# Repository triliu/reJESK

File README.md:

# reJESK

The reJESK, a redox-inspired 70-switch ortholinear keyboard that uses a new diode-free design. 

The diode-free design is easy for first-time keyboard makers, as it reduces the complexity and length of time to make your own board. This keyboard is part of the geometric diode-free keyboard project, which is creating keyboards with great key rollover characteristics without using diodes. Other keyboards released previously are the [Heawood42](https://github.com/triliu/Heawood42) (A 21*2-key split ortholinear board, with 21 keys per 14 GPIO) and the [JESK56](https://github.com/triliu/JESK56) (A 56-key monobody ortholinear board, with 56 keys using 28 GPIO). 

The diode-free design comes from a modification of the JESK graph, which was used in the [JESK56 keyboard](https://github.com/triliu/JESK56) to yield a 56-switch keyboard using 28 GPIO without diodes. This has been placed together with a design that is inspired by the [redox keyboard](https://github.com/mattdibi/redox-keyboard). The JESK graph was found by Exoo, Kolokolnikov, Janssen, Salamon; see their [arXiv paper](https://arxiv.org/abs/2307.07308) or [final publication](https://onlinelibrary.wiley.com/doi/10.1002/jgt.23146?af=R)

This repo contains:
- PCB gerbers (production files) and kicad files (PCB design files). See below for easy print instructions. 
- QMK firmware
- 3D model case 
- (soon) build guide

Many thanks to PCBway, who sponsered this project. You can easily print the reJESK keyboard using the project page on PCBway:

If you wish to modify and print the reJESK keyboard, consider using my affiliate link to help me out as I develop further boards: https://pcbway.com/g/oPKu26

"If you aren’t ready for reJESKtion, you aren’t ready for love.” – Marty Rubin

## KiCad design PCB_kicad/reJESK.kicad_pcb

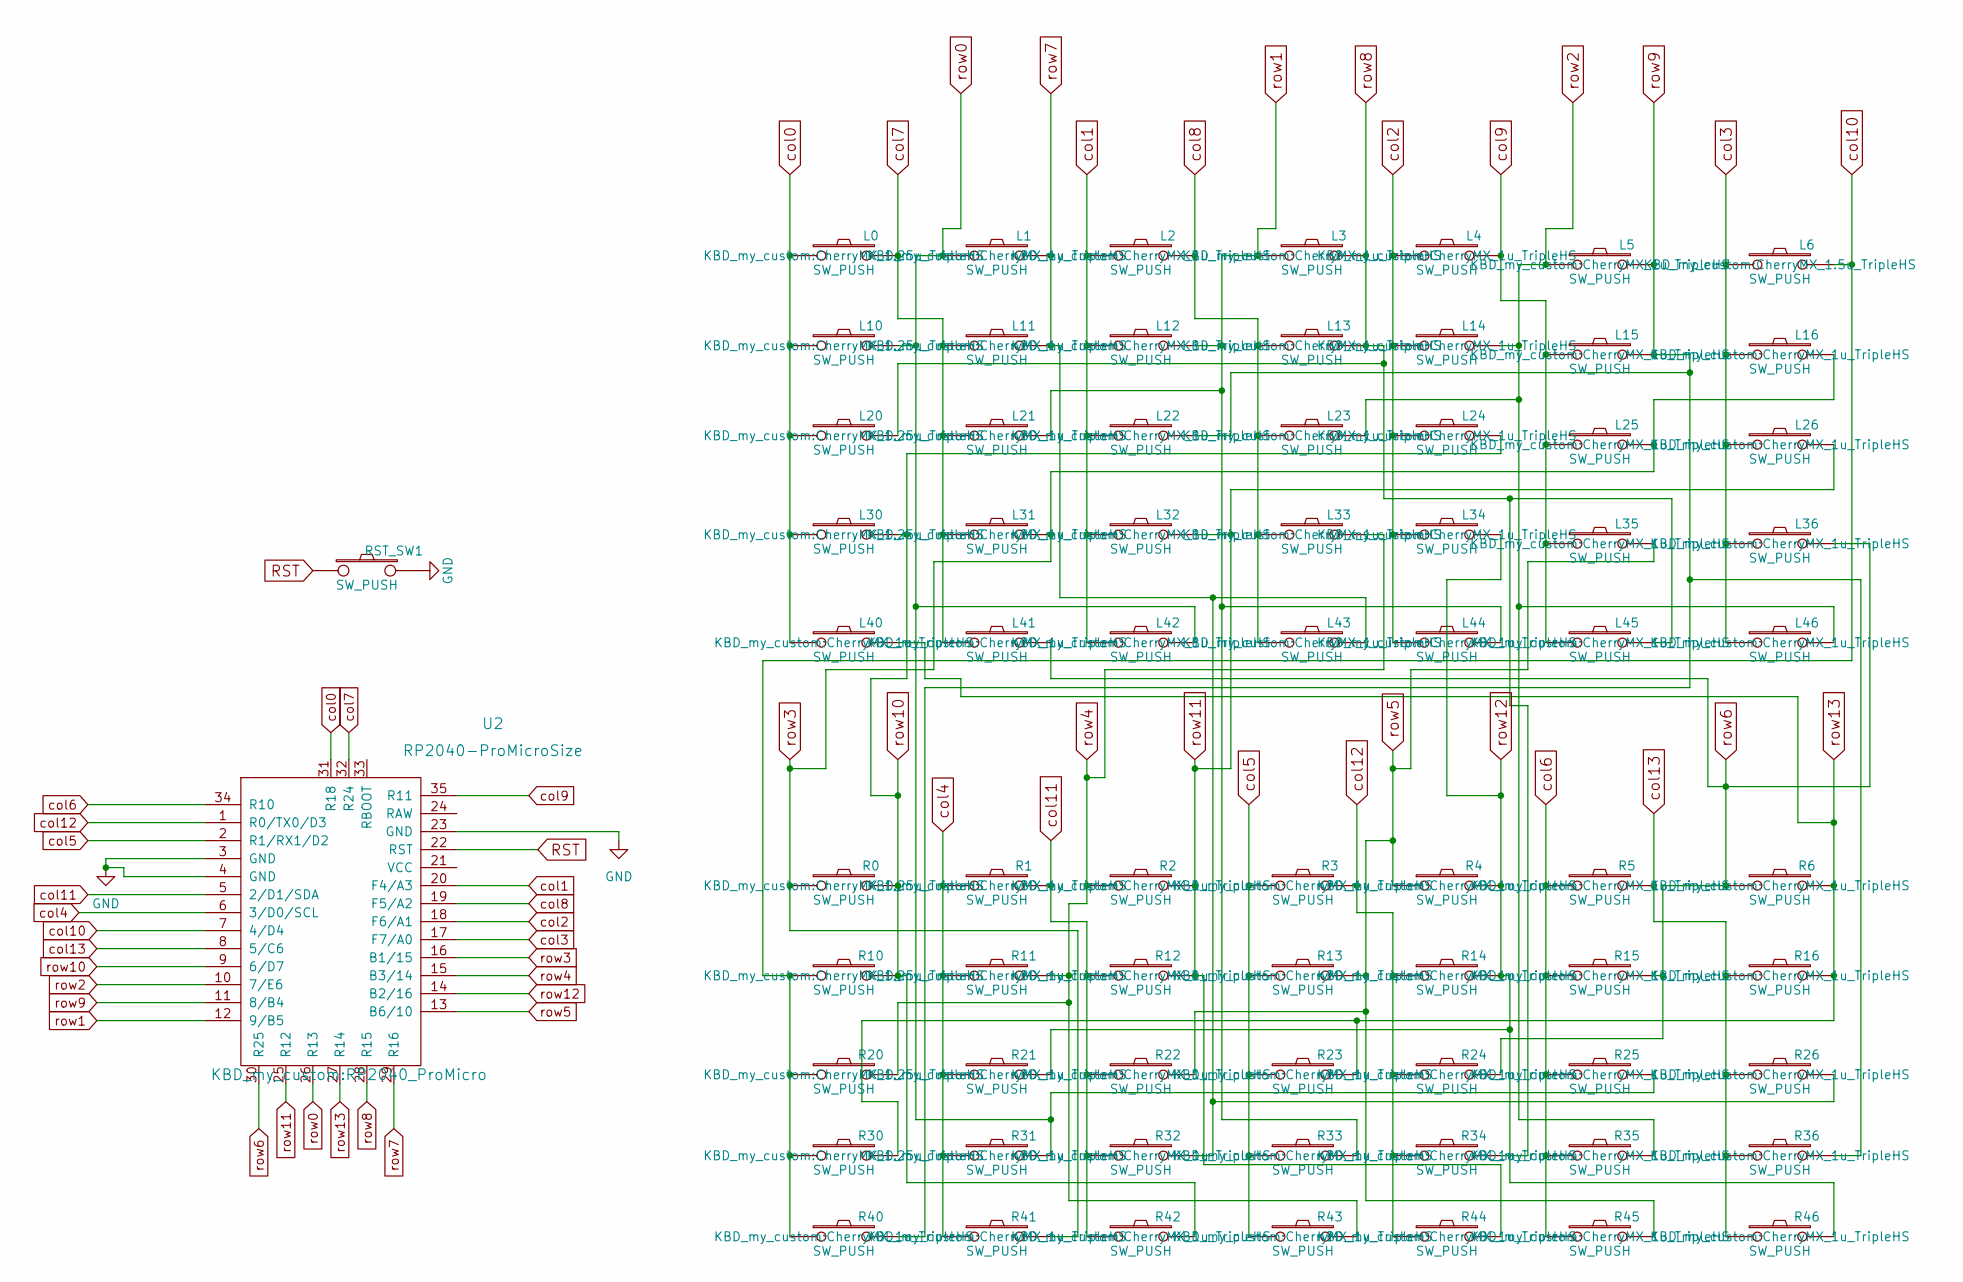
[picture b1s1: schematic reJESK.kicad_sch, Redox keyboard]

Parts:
L0, L10, L20, L30: SW_PUSH; CherryMX_1.25u_TripleHS
L1, L2, L3, L4, L5, L11, L12, L13, L14, L15, L16, L21, L22, L23, L24, L25, L26, L31, L32, L33, L34, L35, L36, L40, L41, L42, L43, L44, L45, L46: SW_PUSH; CherryMX_1u_TripleHS
L6: SW_PUSH; CherryMX_1.5u_TripleHS
R0, R10, R20, R30: SW_PUSH; CherryMX_1.25u_TripleHS
R1, R2, R3, R4, R5, R6, R11, R12, R13, R14, R15, R16, R21, R22, R23, R24, R25, R26, R31, R32, R33, R34, R35, R36, R40, R41, R42, R43, R44, R45, R46: SW_PUSH; CherryMX_1u_TripleHS
RST_SW1: SW_PUSH; SW_PUSH_6mm_h4.3mm
U2: RP2040-ProMicroSize; RP2040_ProMicro

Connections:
GND: RST_SW1.2, U2.3 (GND), U2.4 (GND), U2.23 (GND)
RST: RST_SW1.1, U2.22 (RST)
col0: L0.1, L10.1, L20.1, L30.1, L40.1, U2.31 (R18)
col1: L2.1, L12.1, L22.1, L32.1, L42.1, U2.20 (F4/A3)
col2: L4.1, L14.1, L24.1, L34.1, L44.1, U2.18 (F6/A1)
col3: L6.1, L16.1, L26.1, L36.1, L46.1, U2.17 (F7/A0)
col4: R1.1, R11.1, R21.1, R31.1, R41.1, U2.6 (3/D0/SCL)
col5: R3.1, R13.1, R23.1, R33.1, R43.1, U2.2 (R1/RX1/D2)
col6: R5.1, R15.1, R25.1, R35.1, R45.1, U2.34 (R10)
col7: L0.2, L11.1, L21.1, L31.1, L41.1, U2.32 (R24)
col8: L2.2, L13.1, L23.1, L33.1, L43.1, U2.19 (F5/A2)
col9: L4.2, L15.1, L25.1, L35.1, L45.1, U2.35 (R11)
col10: L6.2, R10.1, R20.1, R30.1, R40.1, U2.7 (4/D4)
col11: R1.2, R12.1, R22.1, R32.1, R42.1, U2.5 (2/D1/SDA)
col12: R3.2, R14.1, R24.1, R34.1, R44.1, U2.1 (R0/TX0/D3)
col13: R5.2, R16.1, R26.1, R36.1, R46.1, U2.8 (5/C6)
row0: L1.1, L10.2, L42.2, R25.2, R31.2, U2.26 (R13)
row1: L3.1, L12.2, L21.2, L44.2, R33.2, U2.12 (9/B5)
row2: L5.1, L14.2, L23.2, L46.2, R35.2, U2.10 (7/E6)
row3: L16.2, L25.2, L31.2, R0.1, R41.2, U2.16 (B1/15)
row4: L33.2, R2.1, R11.2, R20.2, R43.2, U2.15 (B3/14)
row5: L35.2, R4.1, R13.2, R22.2, R45.2, U2.13 (B6/10)
row6: L36.2, L41.2, R6.1, R15.2, R24.2, U2.30 (R25)
row7: L1.2, L11.2, L43.2, R26.2, R32.2, U2.29 (R16)
row8: L3.2, L13.2, L20.2, L45.2, R34.2, U2.28 (R15)
row9: L5.2, L15.2, L22.2, R36.2, R40.2, U2.11 (8/B4)
row10: L24.2, L30.2, R0.2, R10.2, R42.2, U2.9 (6/D7)
row11: L26.2, L32.2, R2.2, R12.2, R44.2, U2.25 (R12)
row12: L34.2, R4.2, R14.2, R21.2, R46.2, U2.14 (B2/16)
row13: L40.2, R6.2, R16.2, R23.2, R30.2, U2.27 (R14)

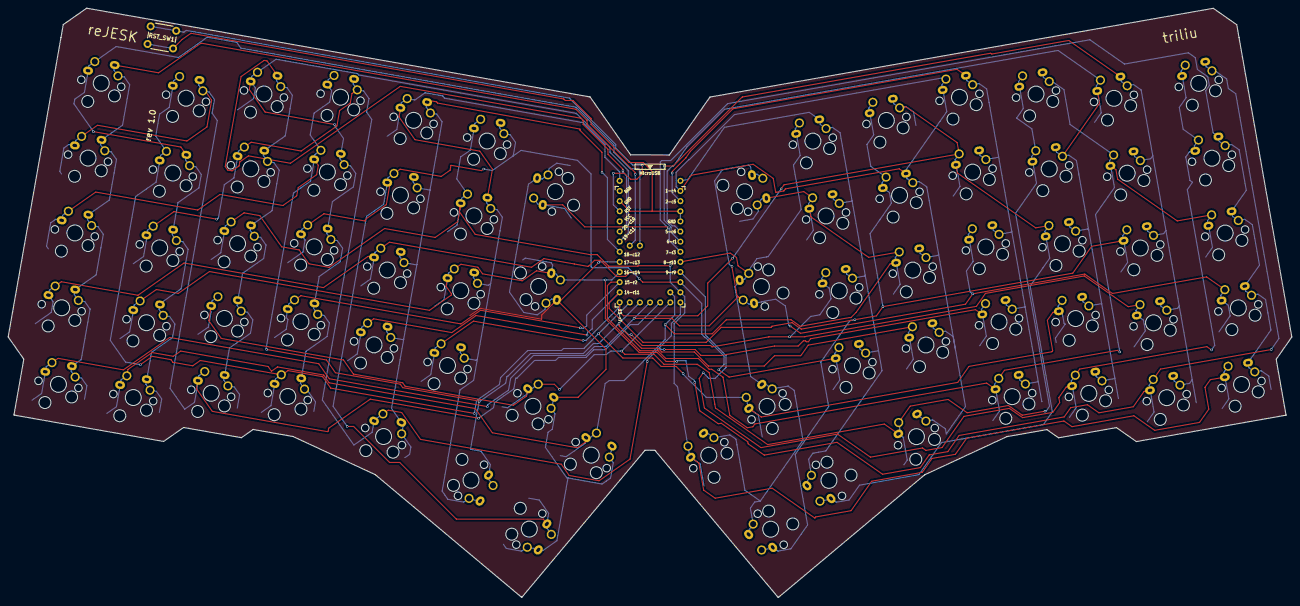
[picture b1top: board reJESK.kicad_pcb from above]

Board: 2 copper layers, 321.8 x 147.7 mm, 72 parts (0 on the bottom side), 30 nets.

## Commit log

2024-09-29 Main Release
2024-09-30 Update README.md
    Update for public release
